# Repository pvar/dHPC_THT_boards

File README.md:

# dHPC

## What is this?

dHPC stands for deltaHacker PC and it's a small **home-brew** computer. It's not only small
in size, but in performance too! The capabilities of this tiny system resemble those of the 80's
home computers. It was built as a project for [deltaHacker magazine][delta], an ethical hacking
magazine, that occasionally hosts articles about electronics.

## What can I do with it?

The computer.* files in this repository were created with [Eagle][eagle], a popular choice for
PCB design among makers and students. In order to view the schematics or the PCB, you need to
download the free version of the program. Alternatively, you could use the on-line viewer that
many board manufacturers facilitate on their websites. You can find a noteworthy viewer of this
kind at [EuroCircuits][euro].

## Is it possible to make one?

Of course it is! Keep in mind, though, that the three microcontrollers which comprise the system
need to be "burnt" with the appropriate firmware. This means you'll need a programmer for AVR
microcontrollers, such as [this one][avrisp]. If you have no idea what a programmer is, you'll
need the help of some electronics tinkerer/hobbyist/engineer.

## I'm good to go! Where is the firmware?

You can find the source code for the firmware of each sub-system in the relevant repository:

* [For the CPU][cpu] (source code in C)
* [For the GPU][gpu] (source code in ASM and the "compiled" HEX)
* [For the APU][apu] (source code in ASM and the "compiled" HEX)

[delta]:    http://deltahacker.gr                       "ethical hacking magazine"
[eagle]:    http://cadsoft.io                           "Eagle PCB design"
[euro]:     http://www.eurocircuits.com                 "EuroCircuit PCB services"
[avrisp]:   http://www.atmel.com/tools/AVRISPMKII.aspx  "AVR ISP programmer homepage"
[cpu]:      https://github.com/pvar/nstBASIC            "firmware for the main processor"
[gpu]:      https://github.com/pvar/dhpc_gpu_firmware   "firmware for the graphics processor"
[apu]:      https://github.com/pvar/dhpc_apu_firmware   "firmware for the sound processor"

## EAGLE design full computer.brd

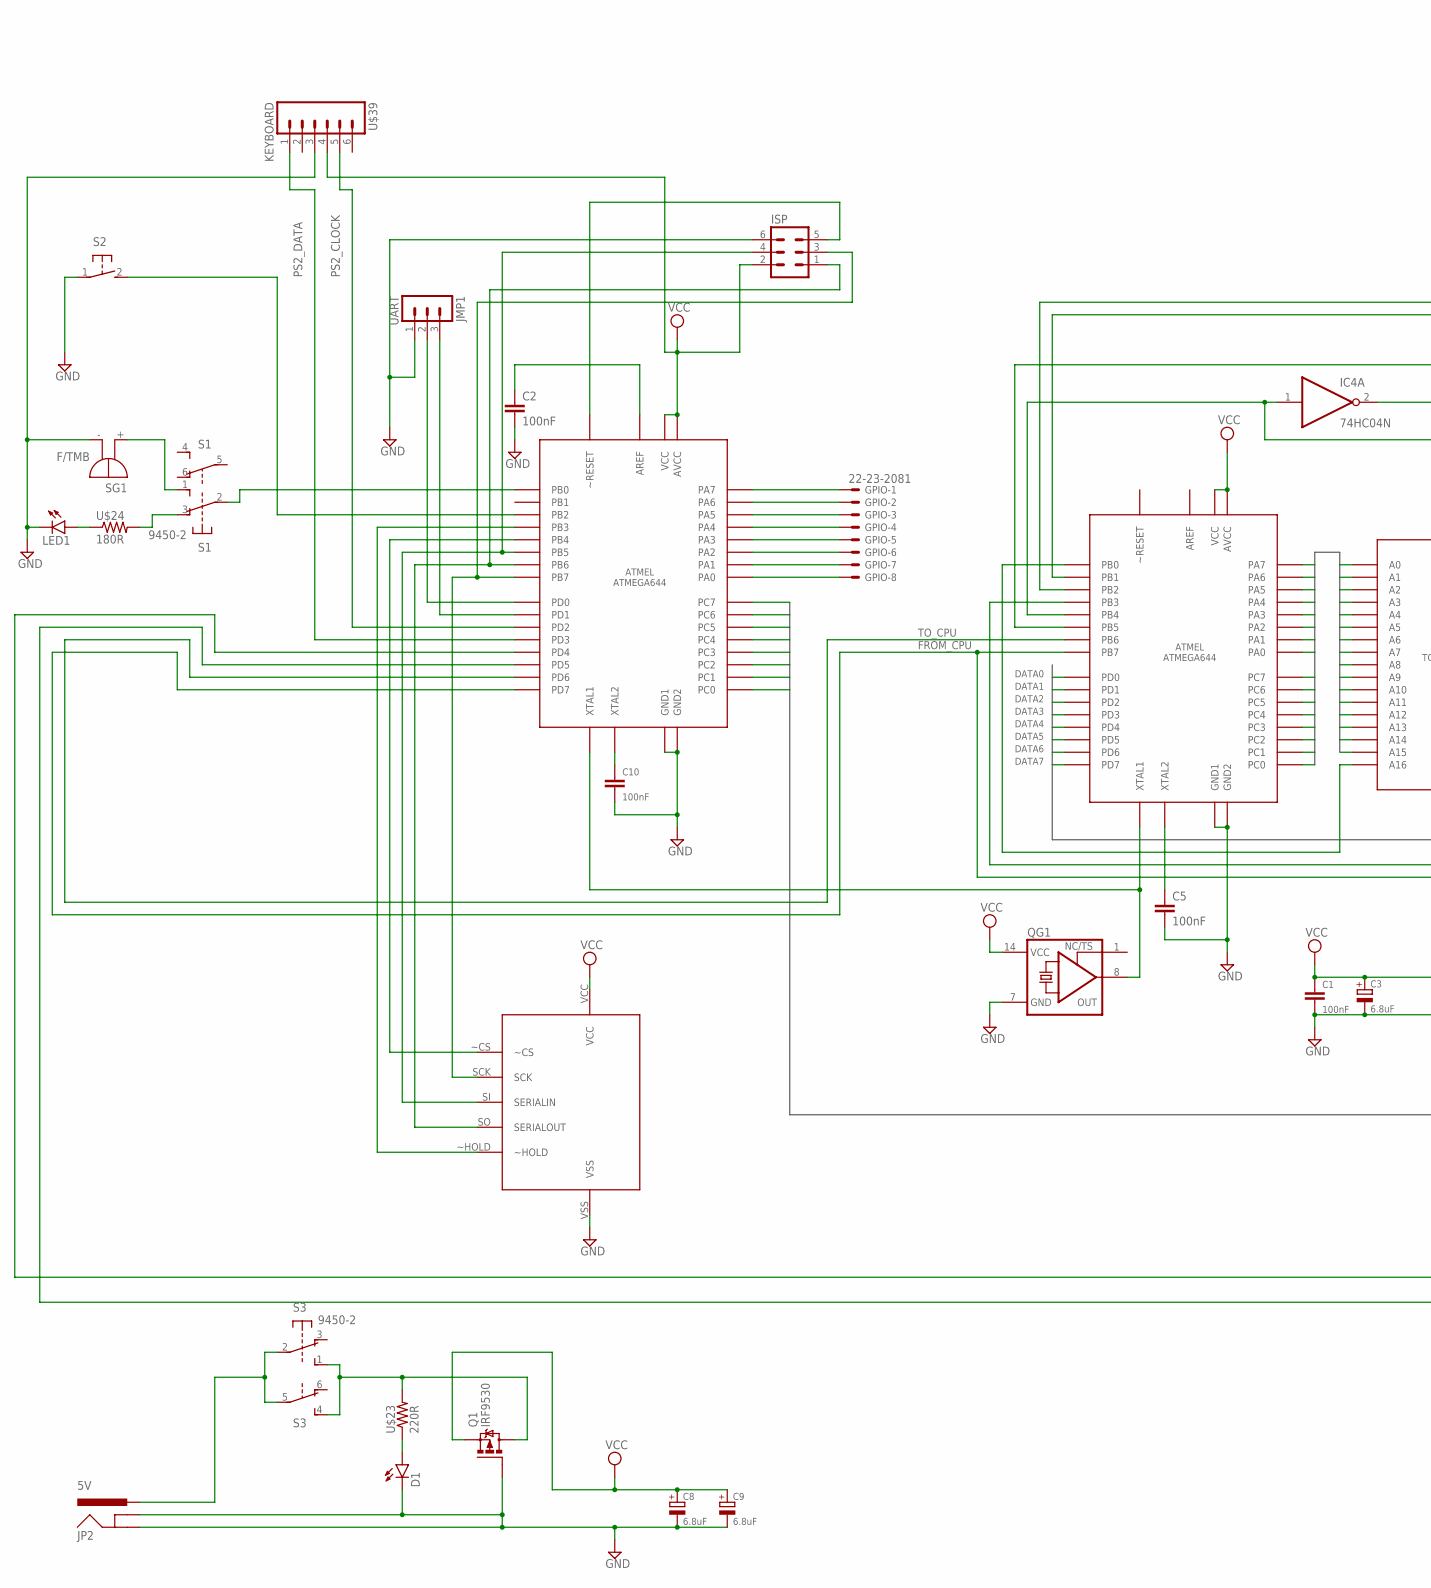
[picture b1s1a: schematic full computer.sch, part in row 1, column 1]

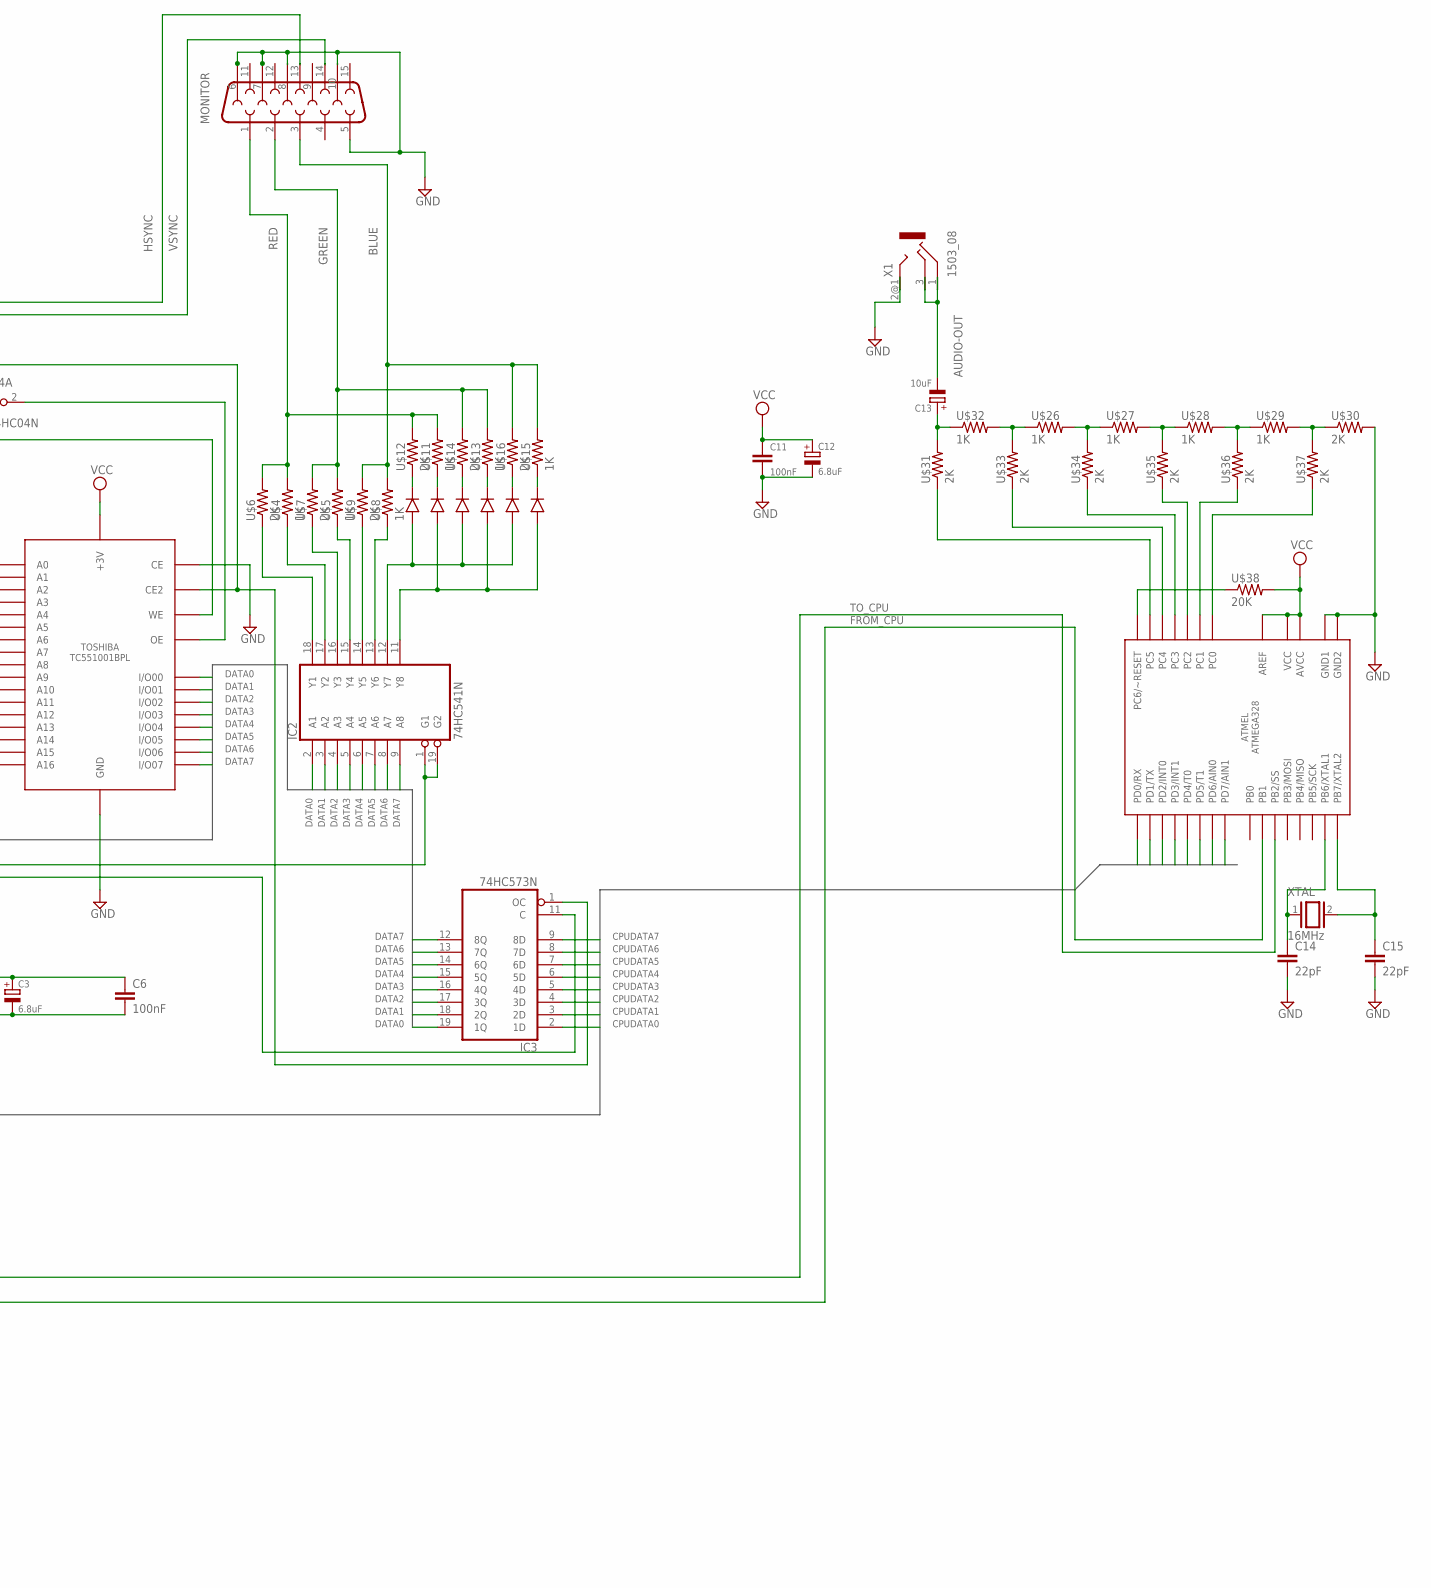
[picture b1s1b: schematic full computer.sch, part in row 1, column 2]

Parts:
C1, C10, C11: 100nF; C5B2.5
C2, C5, C6: 100nF; CAP-PTH-SMALLEZ
C3, C8, C9, C12: 6.8uF; E5-5
C13: 10uF; E5-5
C14, C15: 22pF; CAP-PTH-SMALLEZ
D1: LED5MM
GPIO: 22-23-2081
IC2: 74HC541N; DIL20
IC3: 74HC573N; DIL20
IC4: 74HC04N; DIL14
ISP: ML6
JMP1: UART; MA03-1
JP2: 5V; POWER_JACK_PTH
LED1: LED5MM
Q1: IRF9530; TO220BV
QG1: XO-14; DIL14S
S1, S3: 9450-2
S2: 31-XX; B3F-31XX
SG1: F/TMB
U$1, U$2: ATMEGA644
U$3: TC551001BPL
U$4, U$5, U$8, U$11, U$13, U$15, U$26, U$27, U$28, U$29, U$32: 1K; AXIAL-0.3EZ
U$6, U$7, U$9, U$12, U$14, U$16, U$30, U$31, U$33, U$34, U$35, U$36, U$37: 2K; AXIAL-0.3EZ
U$10: 23LC1024
U$17, U$18, U$19, U$20, U$21, U$22: DIODE
U$23: 220R; AXIAL-0.3EZ
U$24: 180R; AXIAL-0.3EZ
U$25: ATMEGA328
U$38: 20K; AXIAL-0.3EZ
U$39: KEYBOARD; MINI-DIN6
U$40: MONITOR; DB15
X1: 1503_08
XTAL: 16MHz; QS

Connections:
ADDRESS0: U$2.PC0, U$3.A0
ADDRESS1: U$2.PC1, U$3.A1
ADDRESS2: U$2.PC2, U$3.A2
ADDRESS3: U$2.PC3, U$3.A3
ADDRESS4: U$2.PC4, U$3.A4
ADDRESS5: U$2.PC5, U$3.A5
ADDRESS6: U$2.PC6, U$3.A6
ADDRESS7: U$2.PC7, U$3.A7
ADDRESS8: U$2.PA0, U$3.A8
ADDRESS9: U$2.PA1, U$3.A9
ADDRESS10: U$2.PA2, U$3.A10
ADDRESS11: U$2.PA3, U$3.A11
ADDRESS12: U$2.PA4, U$3.A12
ADDRESS13: U$2.PA5, U$3.A13
ADDRESS14: U$2.PA6, U$3.A14
ADDRESS15: U$2.PA7, U$3.A15
AUDIO-OUT: C13.-, X1.1, X1.3
BLUE: U$8.P$2 (2), U$9.P$2 (2), U$15.P$2 (2), U$16.P$2 (2), U$40.3
CPUDATA0: IC3.2 (1D), U$1.PC0, U$25.PD0/RX
CPUDATA1: IC3.3 (2D), U$1.PC1, U$25.PD1/TX
CPUDATA2: IC3.4 (3D), U$1.PC2, U$25.PD2/INT0
CPUDATA3: IC3.5 (4D), U$1.PC3, U$25.PD3/INT1
CPUDATA4: IC3.6 (5D), U$1.PC4, U$25.PD4/T0
CPUDATA5: IC3.7 (6D), U$1.PC5, U$25.PD5 (PD5/T1)
CPUDATA6: IC3.8 (7D), U$1.PC6, U$25.PD6 (PD6/AIN0)
CPUDATA7: IC3.9 (8D), U$1.PC7, U$25.PD7 (PD7/AIN1)
DATA0: IC2.2 (A1), IC3.19 (1Q), U$2.PD0, U$3.I/O1 (I/O00)
DATA1: IC2.3 (A2), IC3.18 (2Q), U$2.PD1, U$3.I/O2 (I/O01)
DATA2: IC2.4 (A3), IC3.17 (3Q), U$2.PD2, U$3.I/O3 (I/O02)
DATA3: IC2.5 (A4), IC3.16 (4Q), U$2.PD3, U$3.I/O4 (I/O03)
DATA4: IC2.6 (A5), IC3.15 (5Q), U$2.PD4, U$3.I/O5 (I/O04)
DATA5: IC2.7 (A6), IC3.14 (6Q), U$2.PD5, U$3.I/O6 (I/O05)
DATA6: IC2.8 (A7), IC3.13 (7Q), U$2.PD6, U$3.I/O7 (I/O06)
DATA7: IC2.9 (A8), IC3.12 (8Q), U$2.PD7, U$3.I/O8 (I/O07)
FROM_CPU: IC3.11 (C), U$1.PD5, U$1.PD7, U$2.PB7, U$25.PB1
GND: C1.2, C2.2, C3.-, C5.2, C6.2, C8.-, C9.-, C10.2, C11.2, C12.-, C14.2, C15.2, D1.K (C), IC2.10 (GND), IC3.10 (GND), IC4.7 (GND), ISP.6, JMP1.1, JP2.GND, JP2.GNDBREAK, LED1.K (C), Q1.G, QG1.7 (GND), S2.1, SG1.-, U$1.GND (GND1), U$1.GND.1 (GND2), U$2.GND (GND1), U$2.GND.1 (GND2), U$3.GND, U$3.~CE1 (CE), U$10.VSS, U$25.GND (GND1), U$25.GND1 (GND2), U$30.P$2 (2), U$39.3, U$40.5, U$40.6, U$40.7, U$40.8, U$40.10, X1.2@1 (2), X1.2@2 (2)
GREEN: U$5.P$2 (2), U$7.P$2 (2), U$13.P$2 (2), U$14.P$2 (2), U$40.2
HSYNC: U$2.PB2, U$40.13
unnamed: QG1.8 (OUT), U$1.XTAL1, U$2.XTAL1
unnamed: U$12.P$1 (1), U$17.CA (CATHODE)
unnamed: IC4.2 (O), U$3.~OE (OE)
unnamed: GPIO.1, U$1.PA7
unnamed: U$2.PB0, U$3.A16
unnamed: IC2.1 (G1), IC2.19 (G2), U$2.PB3
unnamed: C5.1, U$2.XTAL2
unnamed: IC3.1 (OC), U$2.PB5, U$3.CE2
unnamed: C13.+, U$31.P$2 (2), U$32.P$1 (1)
unnamed: IC4.1 (I), U$2.PB4, U$3.R/W (WE)
unnamed: C10.1, U$1.XTAL2
unnamed: U$11.P$1 (1), U$18.CA (CATHODE)
unnamed: U$14.P$1 (1), U$19.CA (CATHODE)
unnamed: U$13.P$1 (1), U$20.CA (CATHODE)
unnamed: U$16.P$1 (1), U$21.CA (CATHODE)
unnamed: U$15.P$1 (1), U$22.CA (CATHODE)
unnamed: JP2.PWR, S3.2, S3.5
unnamed: S1.1 (S), SG1.+
unnamed: S1.3 (O), U$24.P$2 (2)
unnamed: LED1.A, U$24.P$1 (1)
unnamed: S1.2, U$1.PB0
unnamed: JMP1.2, U$1.PD0
unnamed: IC2.18 (Y1), U$6.P$1 (1)
unnamed: IC2.17 (Y2), U$4.P$1 (1)
unnamed: IC2.16 (Y3), U$7.P$1 (1)
unnamed: IC2.15 (Y4), U$5.P$1 (1)
unnamed: IC2.14 (Y5), U$9.P$1 (1)
unnamed: IC2.13 (Y6), U$8.P$1 (1)
unnamed: IC2.12 (Y7), U$17.AN (ANODE), U$19.AN (ANODE), U$21.AN (ANODE)
unnamed: IC2.11 (Y8), U$18.AN (ANODE), U$20.AN (ANODE), U$22.AN (ANODE)
unnamed: U$26.P$1 (1), U$32.P$2 (2), U$33.P$2 (2)
unnamed: U$26.P$2 (2), U$27.P$1 (1), U$34.P$2 (2)
unnamed: U$27.P$2 (2), U$28.P$1 (1), U$35.P$2 (2)
unnamed: U$28.P$2 (2), U$29.P$1 (1), U$36.P$2 (2)
unnamed: U$29.P$2 (2), U$30.P$1 (1), U$37.P$2 (2)
unnamed: U$25.PC5/ADC5 (PC5), U$31.P$1 (1)
unnamed: U$25.PC4/ADC4 (PC4), U$33.P$1 (1)
unnamed: U$25.PC3/ADC3 (PC3), U$34.P$1 (1)
unnamed: U$25.PC2/ADC2 (PC2), U$35.P$1 (1)
unnamed: U$25.PC1/ADC1 (PC1), U$36.P$1 (1)
unnamed: U$25.PC0/ADC0 (PC0), U$37.P$1 (1)
unnamed: U$25.PC6/RESET (PC6/~RESET), U$38.P$1 (1)
unnamed: C14.1, U$25.PB6 (PB6/XTAL1), XTAL.1
unnamed: C15.1, U$25.PB7 (PB7/XTAL2), XTAL.2
unnamed: C2.1, U$1.AREF
unnamed: JMP1.3, U$1.PD1
unnamed: ISP.3, U$1.PB7, U$10.SCK
unnamed: S2.2 (S), U$1.PB2
unnamed: ISP.1, U$1.PB6, U$10.SO (SERIALOUT)
unnamed: ISP.4, U$1.PB5, U$10.SI (SERIALIN)
unnamed: U$1.PB4, U$10.~CS
unnamed: U$1.PB3, U$10.~HOLD
unnamed: GPIO.2, U$1.PA6
unnamed: GPIO.3, U$1.PA5
unnamed: GPIO.4, U$1.PA4
unnamed: GPIO.5, U$1.PA3
unnamed: GPIO.6, U$1.PA2
unnamed: GPIO.7, U$1.PA1
unnamed: GPIO.8, U$1.PA0
unnamed: ISP.5, U$1.~RESET
unnamed: Q1.D, S3.1 (S), S3.4 (S), U$23.P$2 (2)
unnamed: D1.A, U$23.P$1 (1)
PS2_CLOCK: U$1.PD2, U$39.5
PS2_DATA: U$1.PD3, U$39.1
RED: U$4.P$2 (2), U$6.P$2 (2), U$11.P$2 (2), U$12.P$2 (2), U$40.1
TO_CPU: U$1.PD4, U$1.PD6, U$2.PB6, U$25.PB2/SS
VCC: C1.1, C3.+, C6.1, C8.+, C9.+, C11.1, C12.+, IC2.20 (VCC), IC3.20 (VCC), IC4.14 (VCC), ISP.2, Q1.S, QG1.14 (VCC), U$1.AVCC, U$1.VCC, U$2.AVCC, U$2.VCC, U$3.VDD (+3V), U$10.VCC, U$25.AREF, U$25.AVCC, U$25.VCC, U$38.P$2 (2), U$39.4
VSYNC: U$2.PB1, U$40.14

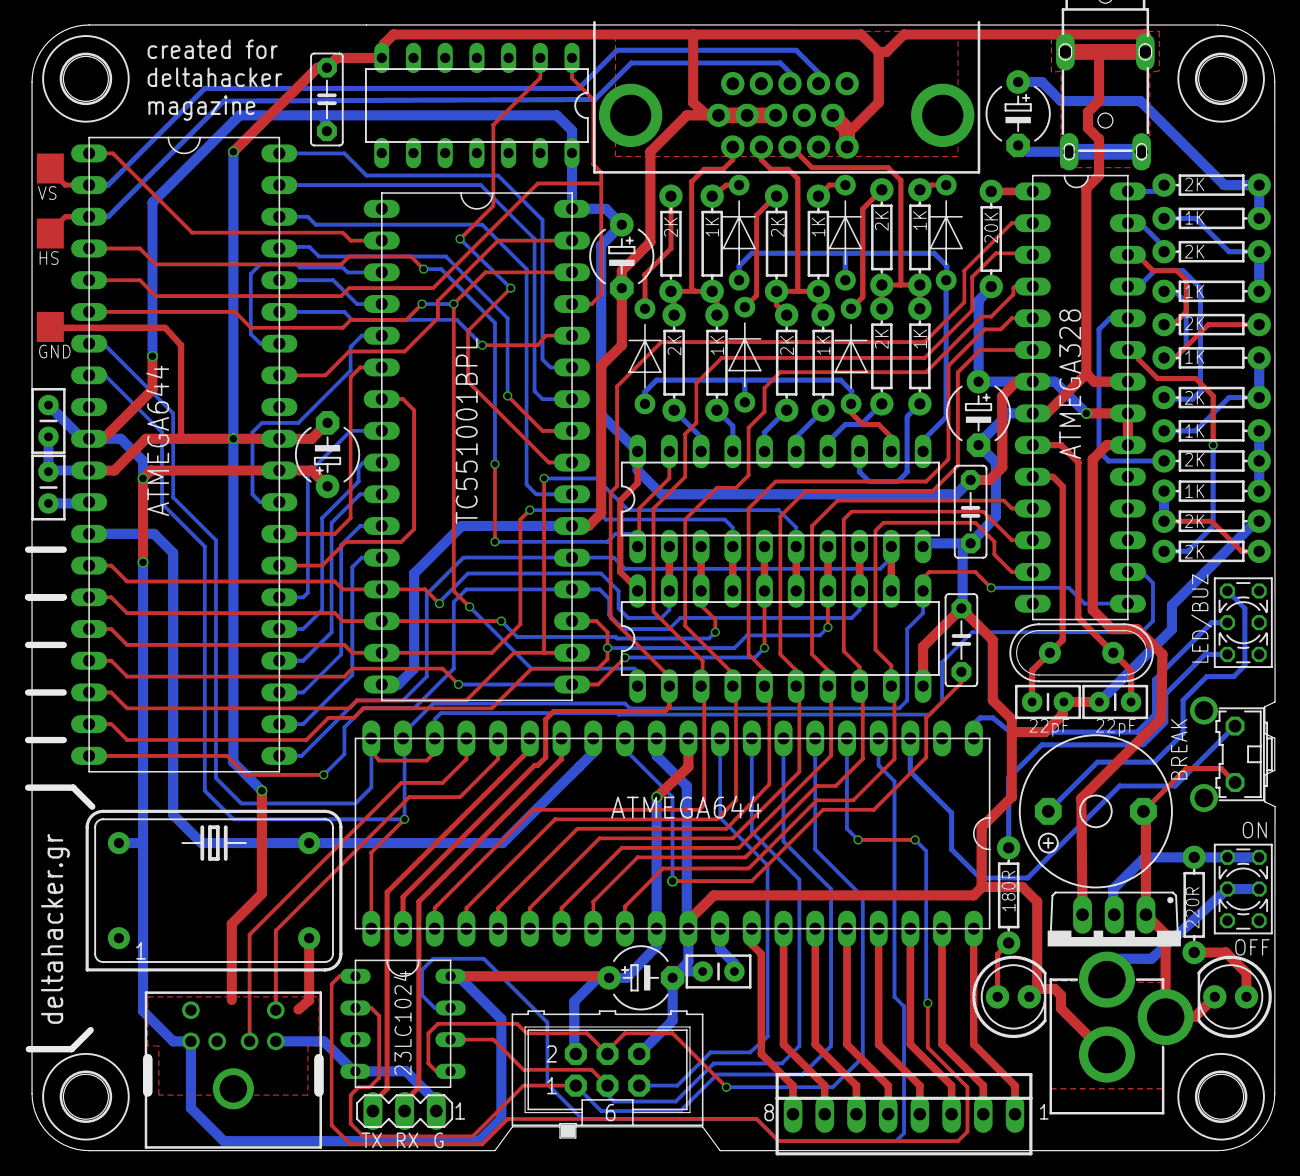
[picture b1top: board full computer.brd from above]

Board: 2 copper layers, 99.6 x 90.2 mm, 74 parts (0 on the bottom side), 106 nets.

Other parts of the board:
H1, H2, H4, H5: MOUNT-HOLE3.0; 3,6

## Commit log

2016-09-13 initial commit: hbpc schematic and pcb
2016-09-13 moved PS2 to rear side and BREAK button to front side, the board is now a bit smaller
2016-09-17 added SD card holder & rounded corners
2016-09-21 removed SD card holder & added external SRAM & reverse voltage protection
2016-10-03 board completely redesigned!
2016-10-03 added test pads for H anv V sync signals
2016-10-03 added more decorative cuts, open hardware logo and some text
2016-10-03 added deltahacker name, decorative cuts and contour curves
2016-10-03 thiner and shorter traces for clock signals, better position for GPIO and SERIAL, schematic clean up
2016-10-03 added README and LICENSE
2016-10-06 minor modifications (mainly to satisfy my OCD)
2017-07-27 fixed some typos in documentation

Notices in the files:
parts and their libraries:
SparkFun-Connectors: Licensing: Creative Commons ShareAlike 4.0 International - https://creativecommons.org/licenses/by-sa/4.0
